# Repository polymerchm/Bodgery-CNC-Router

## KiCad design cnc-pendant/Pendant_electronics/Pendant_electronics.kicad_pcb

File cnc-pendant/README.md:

# ESP32-S3 USB HID CNC Jog Pendant (TechnoCNC LC series)

Ten Cherry MX momentary switches plus three status LEDs (Step, Continuous,
and Enable/armed), acting as a USB keyboard jog pendant over the ESP32-S3
native USB (OTG) port.

## Wiring

Every switch is a simple SPST momentary contact: one terminal to the GPIO,
the other to GND (internal pull-ups enabled, no external resistor needed).

| Function    | GPIO | Type                    | Key sent to host | Notes |
|-------------|------|-------------------------|-------------------|-------|
| +X          | 4    | Axis (tap = 1, hold = stream) | Right arrow       | |
| -X          | 5    | Axis (tap = 1, hold = stream) | Left arrow        | |
| +Y          | 6    | Axis (tap = 1, hold = stream) | Up arrow          | |
| -Y          | 7    | Axis (tap = 1, hold = stream) | Down arrow        | |
| +Z          | 15   | Axis (tap = 1, hold = stream) | Shift+"=" (i.e. "+") | See note below if you meant the numpad "+" |
| -Z          | 16   | Axis (tap = 1, hold = stream) | "-"               | |
| Step        | 17   | Mode select (tap)       | F8                | Lights its LED, turns off Continuous's |
| Continuous  | 18   | Mode select (tap)       | F9                | Lights its LED, turns off Step's |
| Enable      | 8    | Hold 3 s (toggle)       | *(nothing -- local only)* | Does **not** gate any other switch |
| Abort       | 9    | Immediate tap           | Escape            | Always forces the local armed flag off |

The "+"/"-" keys are sent as standard top-row keys (Shift+"=" for "+", plain
"-" for "-"). If TechnoCNC LC actually expects the numpad +/- keys instead,
swap the +Z/-Z entries in `axis_switches[]` for `HID_KEY_KEYPAD_ADD` /
`HID_KEY_KEYPAD_SUBTRACT` (no shift modifier needed for either).

| LED             | GPIO | Lit when                          |
|-----------------|------|------------------------------------|
| Step mode LED   | 10   | Step last selected                |
| Continuous LED  | 11   | Continuous last selected           |
| Enable LED      | 12   | Pendant is armed (Enable held 3 s) |

LED brightness is set by `LED_BRIGHTNESS_PERCENT` near the top of `main.c`
(1 to 100, default 15). The LEDs are PWM-driven by the ESP32-S3's LEDC
hardware at 5 kHz, with a squared curve so the percentage tracks perceived
brightness. Raising the resistor value also dims them, if you prefer.

The LEDs are wired **active-low**: 3V3 -> ~330 ohm resistor -> LED anode,
LED cathode -> GPIO. The firmware pulls the pin LOW to light an LED
(`LED_ACTIVE_LOW` at the top of `main.c`; set it to 0 if you rewire them
GPIO -> resistor -> LED -> GND). The pendant boots disarmed with **all LEDs
dark**. When armed (Enable held 3 s), the Enable LED lights along with the LED
for the current jog mode (Continuous by default, `DEFAULT_MODE` in `main.c`;
0 = Step, 1 = Continuous). Pressing Step or Continuous moves the mode LED.
Disarming -- holding Enable for 3 s again, or instantly by pressing Abort --
turns every LED off. Mode switches still send their keys while disarmed; only
the LEDs are gated. No key is sent at boot.

## Behavior

- **Axis switches (+X/-X/+Y/-Y/+Z/-Z):** typematic-style.
  - A quick tap sends exactly one key press+release -- one character.
  - Holding past 400 ms (`JOG_REPEAT_DELAY_MS`) starts a steady stream of
    key press+release pulses, one every 60 ms (`JOG_REPEAT_INTERVAL_MS`),
    for as long as the switch is held.
  - Releasing stops the stream immediately -- no more characters are sent.
  - Always active (no enable gating).
- **Step / Continuous:** mutually exclusive. Pressing one sends a single key
  tap (not held) and updates the LEDs; the previous mode's LED turns off.
  Always active.
- **Enable:** hold continuously for 3 seconds to toggle an internal
  armed/disarmed flag and its LED along with it. **Nothing is sent to the
  host for this switch** -- it only affects this firmware's own state,
  which Abort force-resets. Releasing before 3 s cancels the attempt. This
  switch does **not** block or gate the axis or mode switches -- all other
  buttons work regardless of the armed state.
- **Abort:** works immediately on a single press, no hold required. Sends
  its key tap right away and always forces the armed state (and its LED)
  to disarmed/off, regardless of what it was. Treat it like a software
  e-stop signal; actual motion stopping still depends on how TechnoCNC LC
  responds to that key.

Change any pin, key, or timing at the top of `main/main.c`
(`axis_switches[]`, `mode_switches[]`, `ENABLE_*`, `ABORT_*`,
`ENABLE_HOLD_MS`, `TAP_DOWN_MS`, `JOG_REPEAT_DELAY_MS`,
`JOG_REPEAT_INTERVAL_MS`).

## Build & flash (ESP-IDF 5.1+)

```
idf.py set-target esp32s3
idf.py build
idf.py -p <PORT> flash monitor
```

The first build downloads `espressif/esp_tinyusb` automatically. This project
pins `^3.0.0` (the current `.descriptor.*`/`.phy.*`-style API), needed for
recent ESP-IDF releases such as 6.0.x. If you've built this before with an
older pin, delete `build/`, `managed_components/`, and
`dependencies.lock` first so the component manager re-resolves cleanly.

## Using the two USB-C ports

- **UART / COM port:** use this one for flashing and the serial monitor.
- **USB (native) port:** plug this into the computer running TechnoCNC LC.

Once TinyUSB is running, the native port becomes the keyboard, so the
built-in USB-Serial-JTAG console is not available on it. If you ever need to
force download mode, hold BOOT, tap RESET, release BOOT.

## Notes

- All switches are debounced (20 ms).
- Every character sent to the host, whether from an axis repeat, a mode
  select, or Abort, is a brief discrete key press+release (15 ms down by
  default via `TAP_DOWN_MS`), not a sustained "key held down" state. If your
  TechnoCNC LC setup needs a true held key instead of a stream of taps for
  continuous jogging, that's a different design -- ask and I can switch it.
- This targets `esp_tinyusb` 3.x's `TINYUSB_DEFAULT_CONFIG()` +
  `.descriptor.*` API. If you intentionally pin an older `esp_tinyusb` 1.x,
  the config struct is flat (`.device_descriptor`, `.string_descriptor`,
  `.configuration_descriptor`, `.external_phy`, no count field) and
  `main.c`'s `app_main()` USB setup block needs rewriting to match.

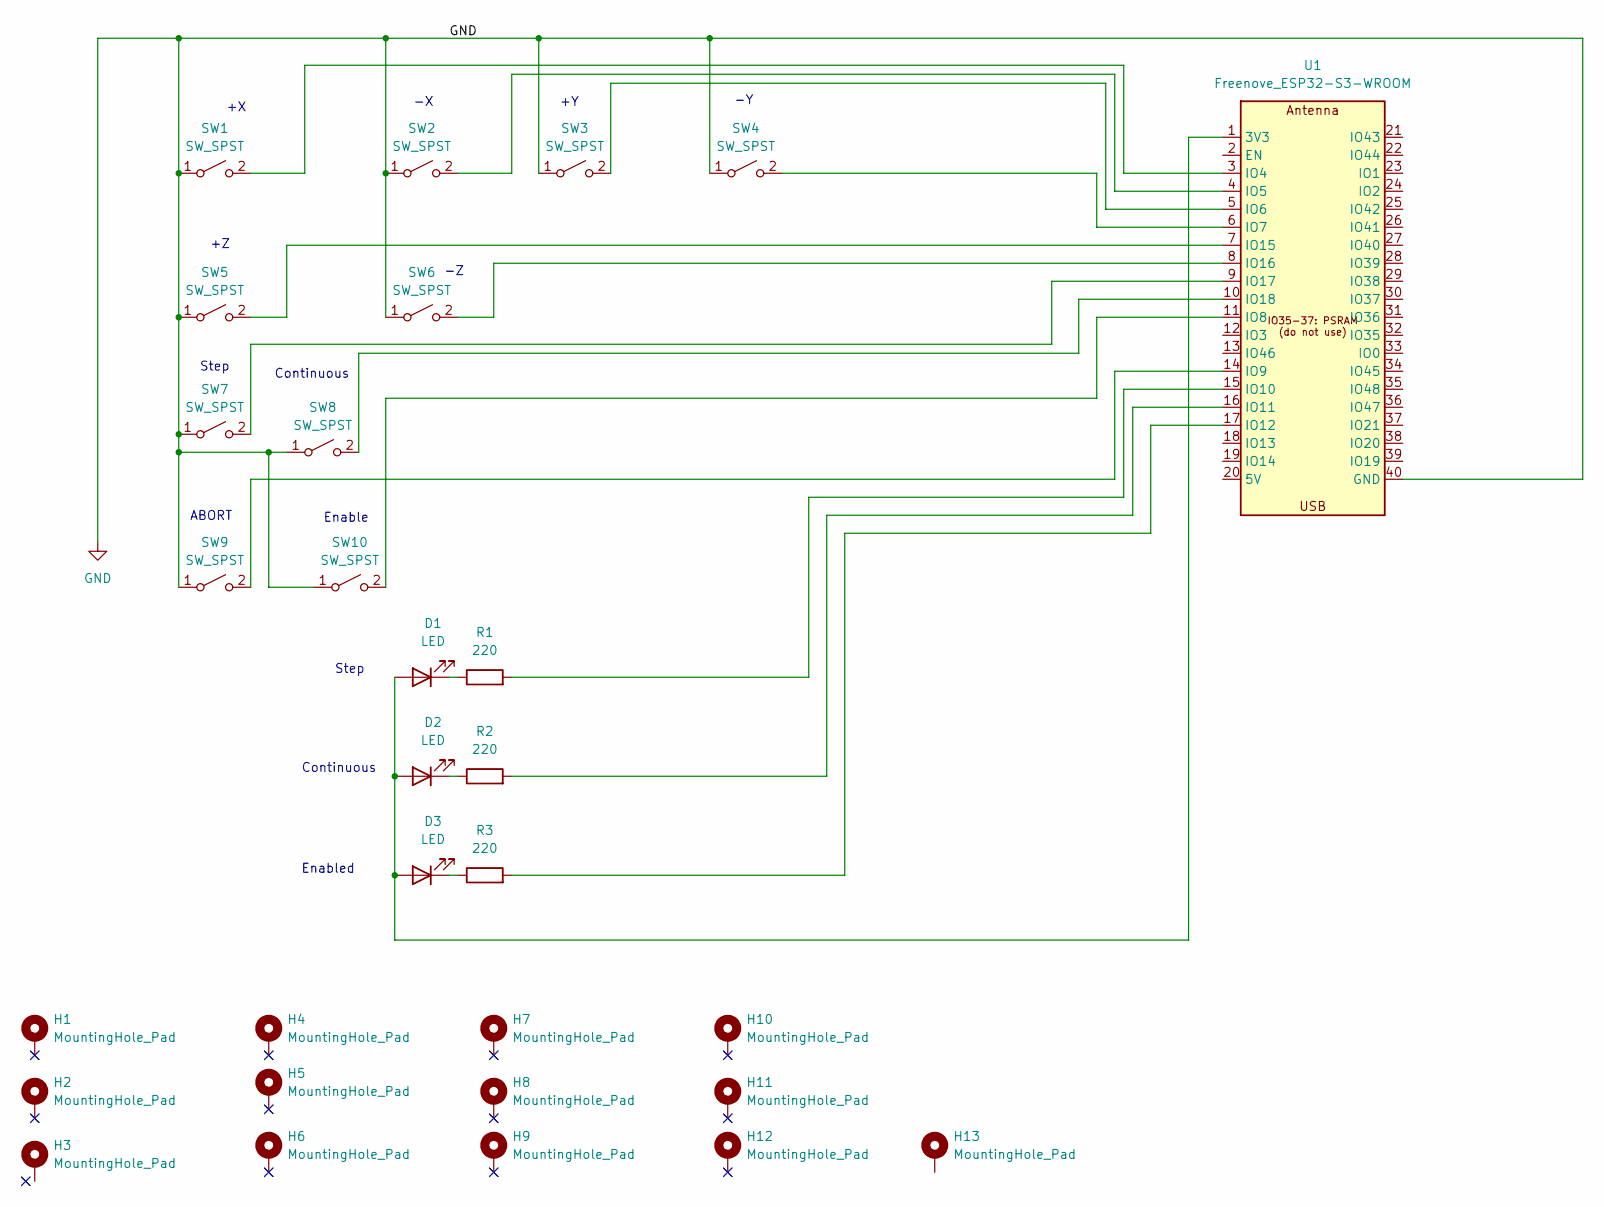
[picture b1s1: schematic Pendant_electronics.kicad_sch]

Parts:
D1, D2, D3: LED; LED_D5.0mm
H1, H2, H3, H4, H5, H6, H7, H8, H9, H10, H11, H12, H13: MountingHole_Pad; MountingHole_2.1mm
R1, R2, R3: 220; R_Axial_DIN0204_L3.6mm_D1.6mm_P5.08mm_Horizontal
SW1, SW2, SW3, SW4, SW5, SW6, SW7, SW8, SW9, SW10: SW_SPST; SW_Cherry_MX_1.00u_Plate
U1: Freenove_ESP32-S3-WROOM

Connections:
GND: SW1.1 (A), SW2.1 (A), SW3.1 (A), SW4.1 (A), SW5.1 (A), SW6.1 (A), SW7.1 (A), SW8.1 (A), SW9.1 (A), SW10.1 (A), U1.40 (GND)
unnamed: D1.2 (A), D2.2 (A), D3.2 (A), U1.1 (3V3)
unnamed: D1.1 (K), R1.1
unnamed: D2.1 (K), R2.1
unnamed: D3.1 (K), R3.1
unnamed: SW1.2 (B), U1.3 (IO4)
unnamed: SW2.2 (B), U1.4 (IO5)
unnamed: SW3.2 (B), U1.5 (IO6)
unnamed: SW4.2 (B), U1.6 (IO7)
unnamed: SW5.2 (B), U1.7 (IO15)
unnamed: SW6.2 (B), U1.8 (IO16)
unnamed: SW7.2 (B), U1.9 (IO17)
unnamed: SW8.2 (B), U1.10 (IO18)
unnamed: SW9.2 (B), U1.14 (IO9)
unnamed: SW10.2 (B), U1.11 (IO8)
unnamed: R1.2, U1.15 (IO10)
unnamed: R2.2, U1.16 (IO11)
unnamed: R3.2, U1.17 (IO12)

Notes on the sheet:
Enabled
Continuous
Step
ABORT
Enable

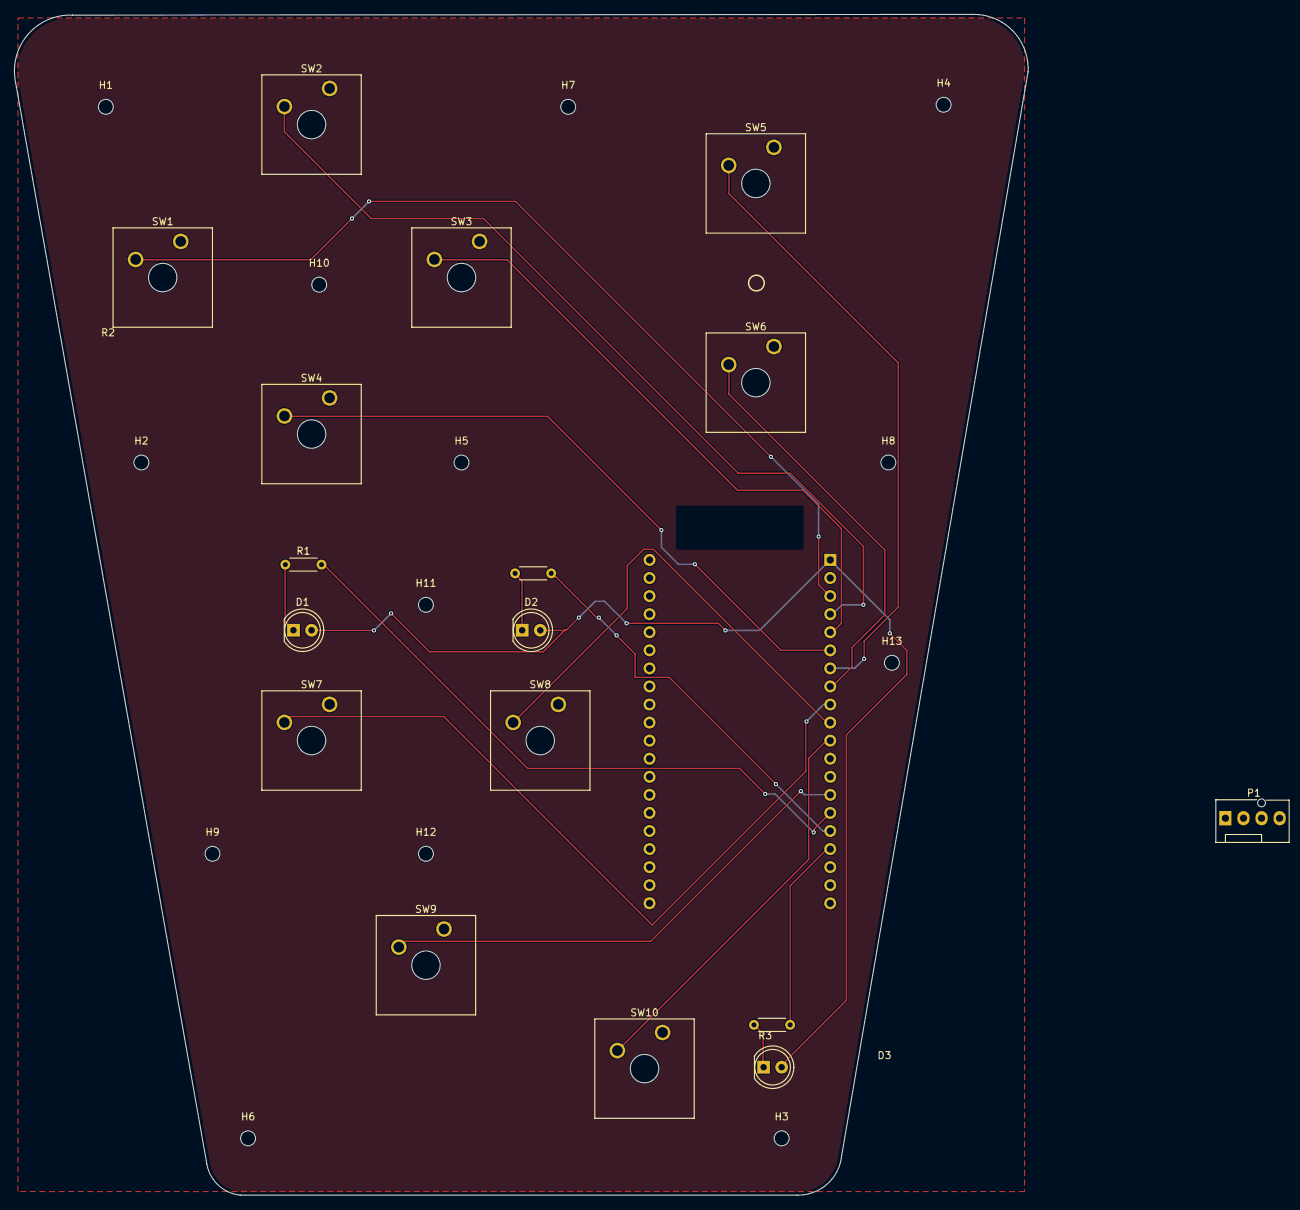
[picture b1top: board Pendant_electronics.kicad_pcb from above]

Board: 2 copper layers, 142.5 x 166.0 mm, 31 parts (1 on the bottom side), 18 nets.

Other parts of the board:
P1: USB_C_Plug_USB2.0; FanPinHeader_1x04_P2.54mm_Vertical

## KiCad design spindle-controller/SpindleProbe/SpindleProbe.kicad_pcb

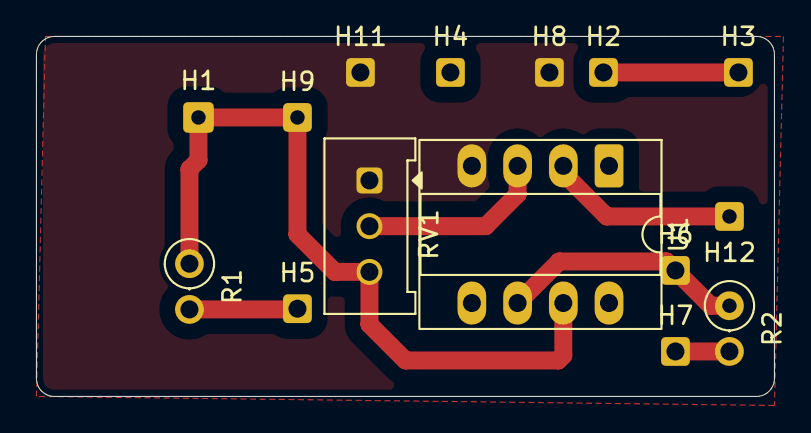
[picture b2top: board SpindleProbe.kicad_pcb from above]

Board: 2 copper layers, 41.0 x 20.0 mm, 15 parts (0 on the bottom side), 8 nets.

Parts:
H1: MountingHole_Pad; SolderWire-0.15sqmm_1x01_D0.5mm_OD1.5mm
H2, H3, H4, H5, H6, H7, H8, H9, H11, H12: MountingHole_Pad; SolderWire-0.1sqmm_1x01_D0.4mm_OD1mm
R1, R2: 330 ohm; R_Axial_DIN0207_L6.3mm_D2.5mm_P2.54mm_Vertical
RV1: R_Potentiometer_Trim; Potentiometer_Bourns_3386W_Horizontal
U1: LM741; CERDIP-8_W7.62mm_SideBrazed_LongPads_Socket

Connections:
/GND: H3.1 (1_1), H8.1 (1_1), H11.1 (1_1), RV1.1, U1.4 (V-)
/VCC: H1.1 (1_1), H9.1 (1_1), R1.1, RV1.3, U1.7 (V+)
unnamed: H2.1 (1_1), H4.1 (1_1)
unnamed: H5.1 (1_1), R1.2
unnamed: H6.1 (1_1), R2.1, U1.6
unnamed: H7.1 (1_1), R2.2
unnamed: RV1.2, U1.3 (+)
unnamed: H12.1 (1_1), U1.2 (-)
